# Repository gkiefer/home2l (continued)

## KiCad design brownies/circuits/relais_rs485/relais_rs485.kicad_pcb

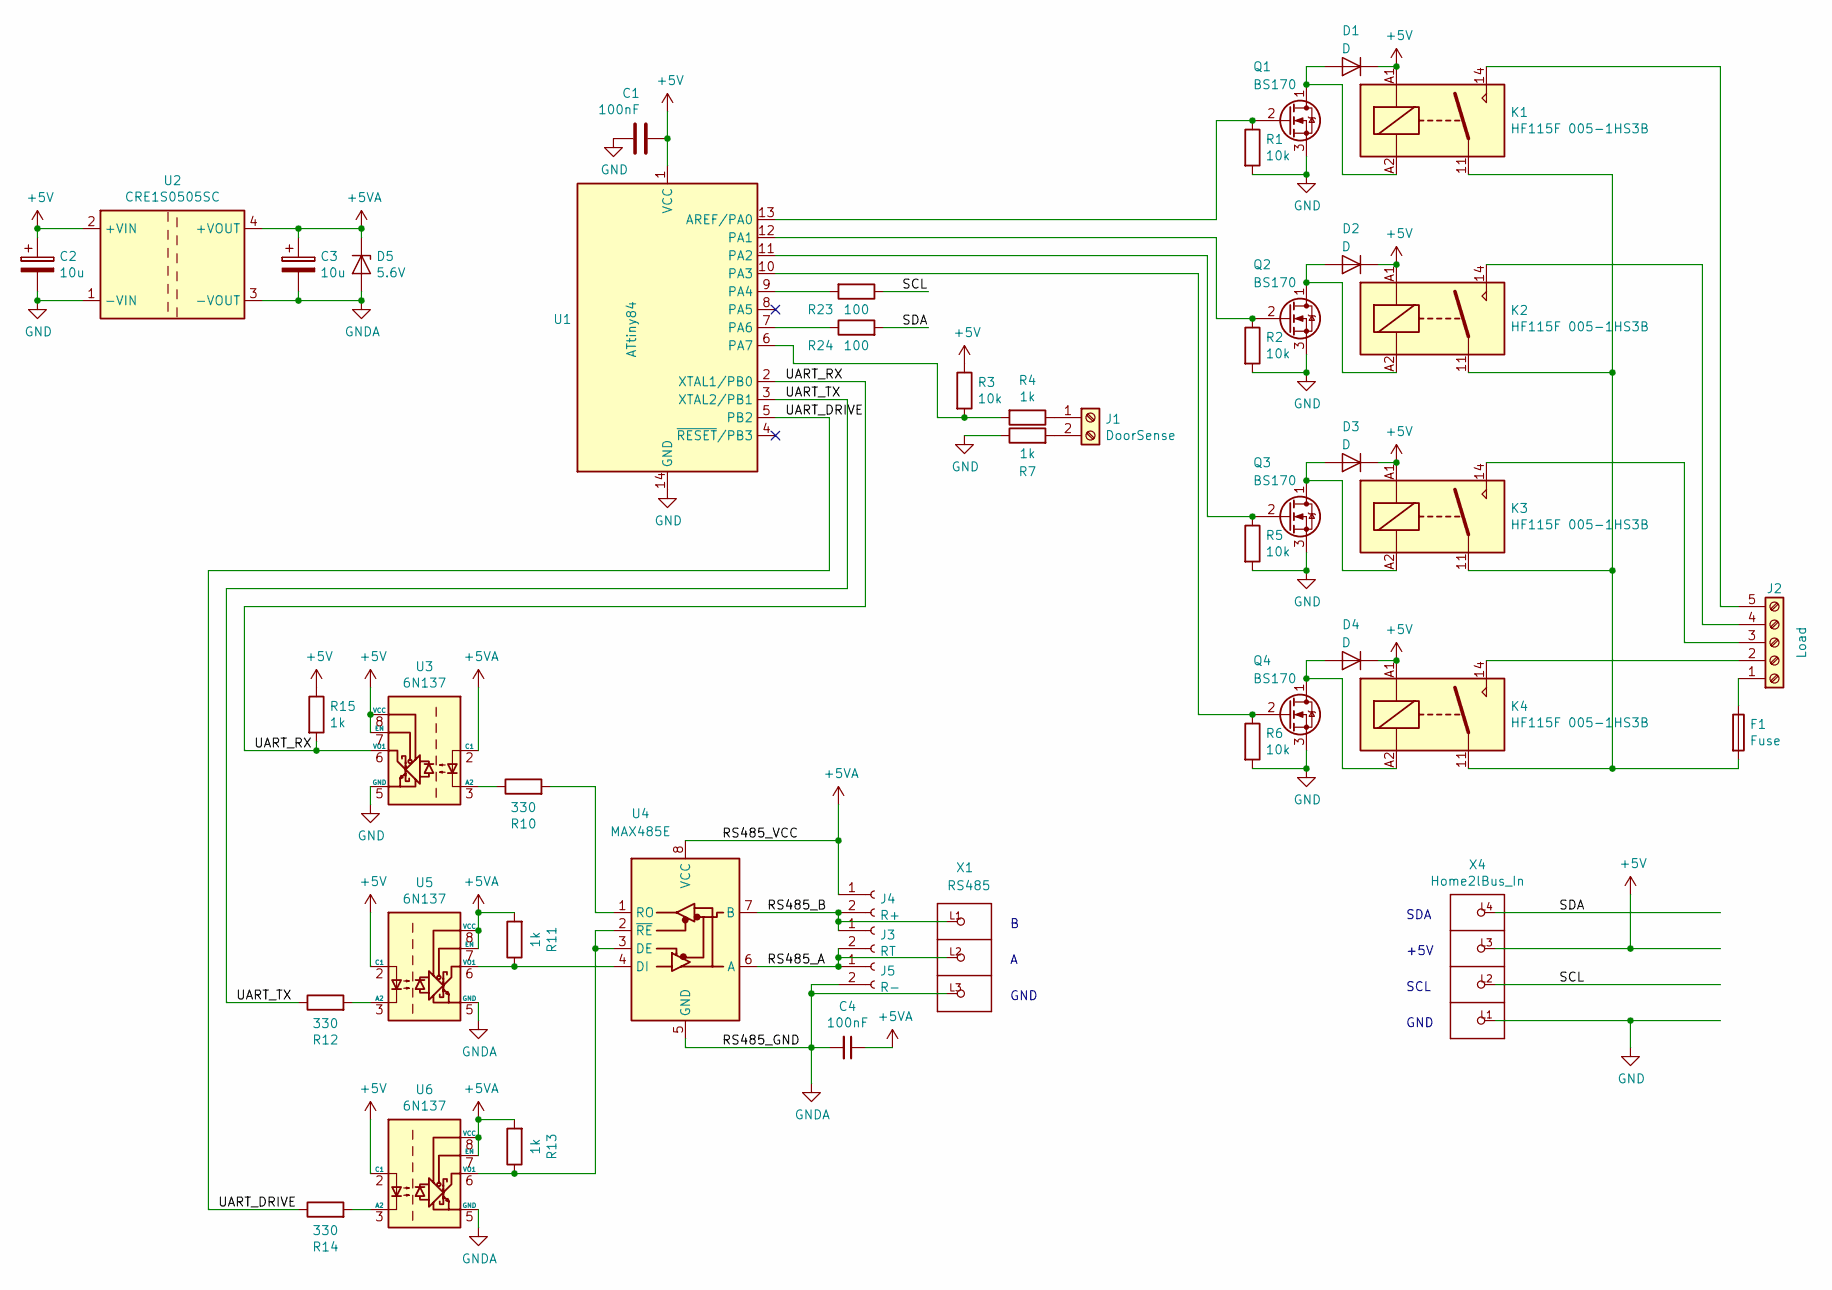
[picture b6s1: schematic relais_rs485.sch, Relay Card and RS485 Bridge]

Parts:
C1: 100nF; C_Disc_D4.3mm_W1.9mm_P5.00mm
C2, C3: 10u; CP_Radial_D5.0mm_P2.50mm
C4: 100nF; C_Axial_L3.8mm_D2.6mm_P7.50mm_Horizontal
D1, D2, D3, D4: D; D_T-1_P5.08mm_Horizontal
D5: 5.6V; D_T-1_P5.08mm_Horizontal
F1: Fuse; Fuseholder_Cylinder-5x20mm_Stelvio-Kontek_PTF78_Horizontal_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
J1: DoorSense; TerminalBlock_Phoenix_MKDS-1,5-2-5.08_1x02_P5.08mm_Horizont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
J2: Load; TerminalBlock_Phoenix_MKDS-1,5-5-5.08_1x05_P5.08mm_Horizont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
J3: RT; PinSocket_1x02_P2.54mm_Vertical
J4: R+; PinSocket_1x02_P2.54mm_Vertical
J5: R-; PinSocket_1x02_P2.54mm_Vertical
K1, K2, K3, K4: HF115F 005-1HS3B; Relay_SPST_Schrack-RP-II-1-16A-FormA_RM5mm
Q1, Q2, Q3, Q4: BS170; TO-92_Inline_Wide
R1, R2, R3, R5, R6: 10k; R_Axial_DIN0204_L3.6mm_D1.6mm_P7.62mm_Horizontal
R4, R7, R11, R13, R15: 1k; R_Axial_DIN0204_L3.6mm_D1.6mm_P7.62mm_Horizontal
R10, R12, R14: 330; R_Axial_DIN0204_L3.6mm_D1.6mm_P7.62mm_Horizontal
R23, R24: 100; R_Axial_DIN0204_L3.6mm_D1.6mm_P7.62mm_Horizontal
U1: ATtiny84; DIP-14_W7.62mm
U2: CRE1S0505SC; Converter_DCDC_muRata_CRE1xxxxxxSC_THT
U3, U5, U6: 6N137; DIP-8_W7.62mm
U4: MAX485E; DIP-8_W7.62mm
X1: RS485; P-250-403
X4: Home2lBus_In; P-250-404

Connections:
+5V: C1.1, C2.1, D1.1 (K), D2.1 (K), D3.1 (K), D4.1 (K), K1.A1, K2.A1, K3.A1, K4.A1, R3.1, R15.1, U1.1 (VCC), U2.2 (+VIN), U3.7 (EN), U3.8 (VCC), U5.2 (C1), U6.2 (C1), X4.L3 (P3)
+5VA: C3.1, C4.1, D5.1 (K), J4.1, R11.2, R13.2, U2.4 (+VOUT), U3.2 (C1), U4.8 (VCC), U5.7 (EN), U5.8 (VCC), U6.7 (EN), U6.8 (VCC)
/RS485_A: J3.2, J5.1, U4.6 (A), X1.L2
/RS485_B: J3.1, J4.2, U4.7 (B), X1.L1
/SCL: R23.1, X4.L2 (P2)
/SDA: R24.2, X4.L4 (P4)
/UART_DRIVE: R14.1, U1.5 (PB2)
/UART_RX: R15.2, U1.2 (XTAL1/PB0), U3.6 (VO1)
/UART_TX: R12.1, U1.3 (XTAL2/PB1)
GND: C1.2, C2.2, Q1.3 (S), Q2.3 (S), Q3.3 (S), Q4.3 (S), R1.2, R2.2, R5.2, R6.2, R7.1, U1.14 (GND), U2.1 (-VIN), U3.5 (GND), X4.L1 (P1)
GNDA: C3.2, C4.2, D5.2 (A), J5.2, U2.3 (-VOUT), U4.5 (GND), U5.5 (GND), U6.5 (GND), X1.L3
unnamed: D1.2 (A), K1.A2, Q1.1 (D)
unnamed: D2.2 (A), K2.A2, Q2.1 (D)
unnamed: D3.2 (A), K3.A2, Q3.1 (D)
unnamed: D4.2 (A), K4.A2, Q4.1 (D)
unnamed: F1.1, J2.1
unnamed: F1.2, K1.11, K2.11, K3.11, K4.11
unnamed: J1.1, R4.1
unnamed: J1.2, R7.2
unnamed: J2.2, K4.14
unnamed: J2.3, K3.14
unnamed: J2.4, K2.14
unnamed: J2.5, K1.14
unnamed: Q1.2 (G), R1.1, U1.13 (AREF/PA0)
unnamed: Q2.2 (G), R2.1, U1.12 (PA1)
unnamed: Q3.2 (G), R5.1, U1.11 (PA2)
unnamed: Q4.2 (G), R6.1, U1.10 (PA3)
unnamed: R3.2, R4.2, U1.6 (PA7)
unnamed: R10.1, U3.3 (A2)
unnamed: R10.2, U4.1 (RO)
unnamed: R11.1, U4.4 (DI), U5.6 (VO1)
unnamed: R12.2, U5.3 (A2)
unnamed: R13.1, U4.2 (~RE), U4.3 (DE), U6.6 (VO1)
unnamed: R14.2, U6.3 (A2)
unnamed: R23.2, U1.9 (PA4)
unnamed: R24.1, U1.7 (PA6)

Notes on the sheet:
SDA
+5V
SCL
GND

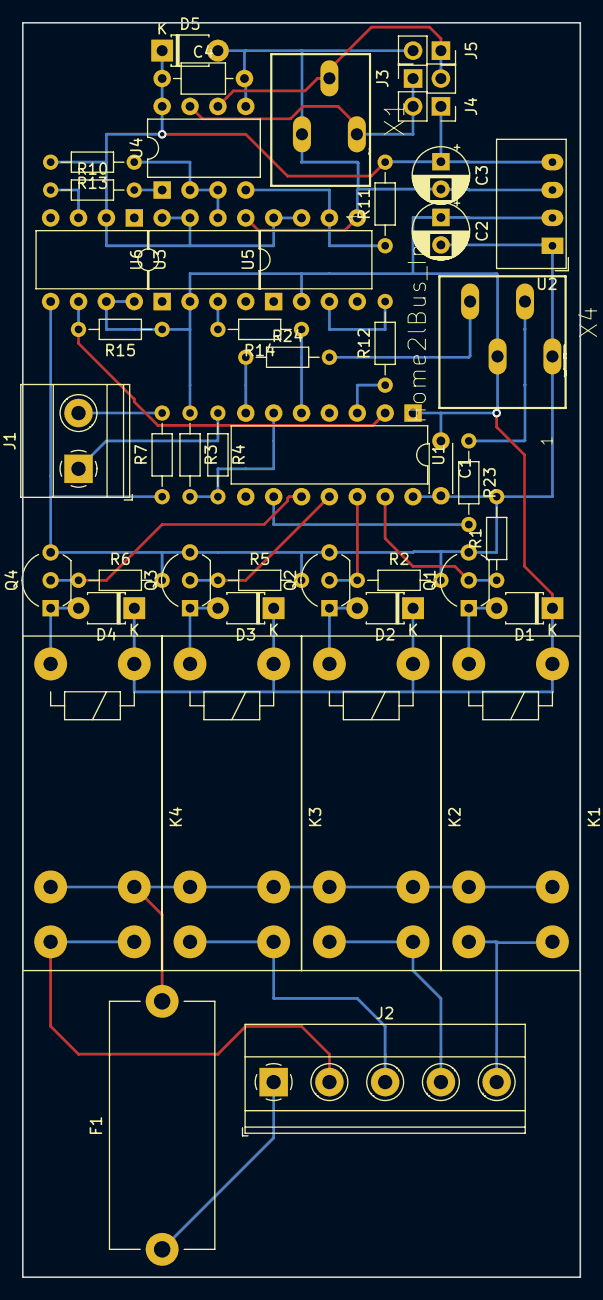
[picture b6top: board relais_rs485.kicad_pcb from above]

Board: 4 copper layers, 50.8 x 114.3 mm, 46 parts (0 on the bottom side), 36 nets.

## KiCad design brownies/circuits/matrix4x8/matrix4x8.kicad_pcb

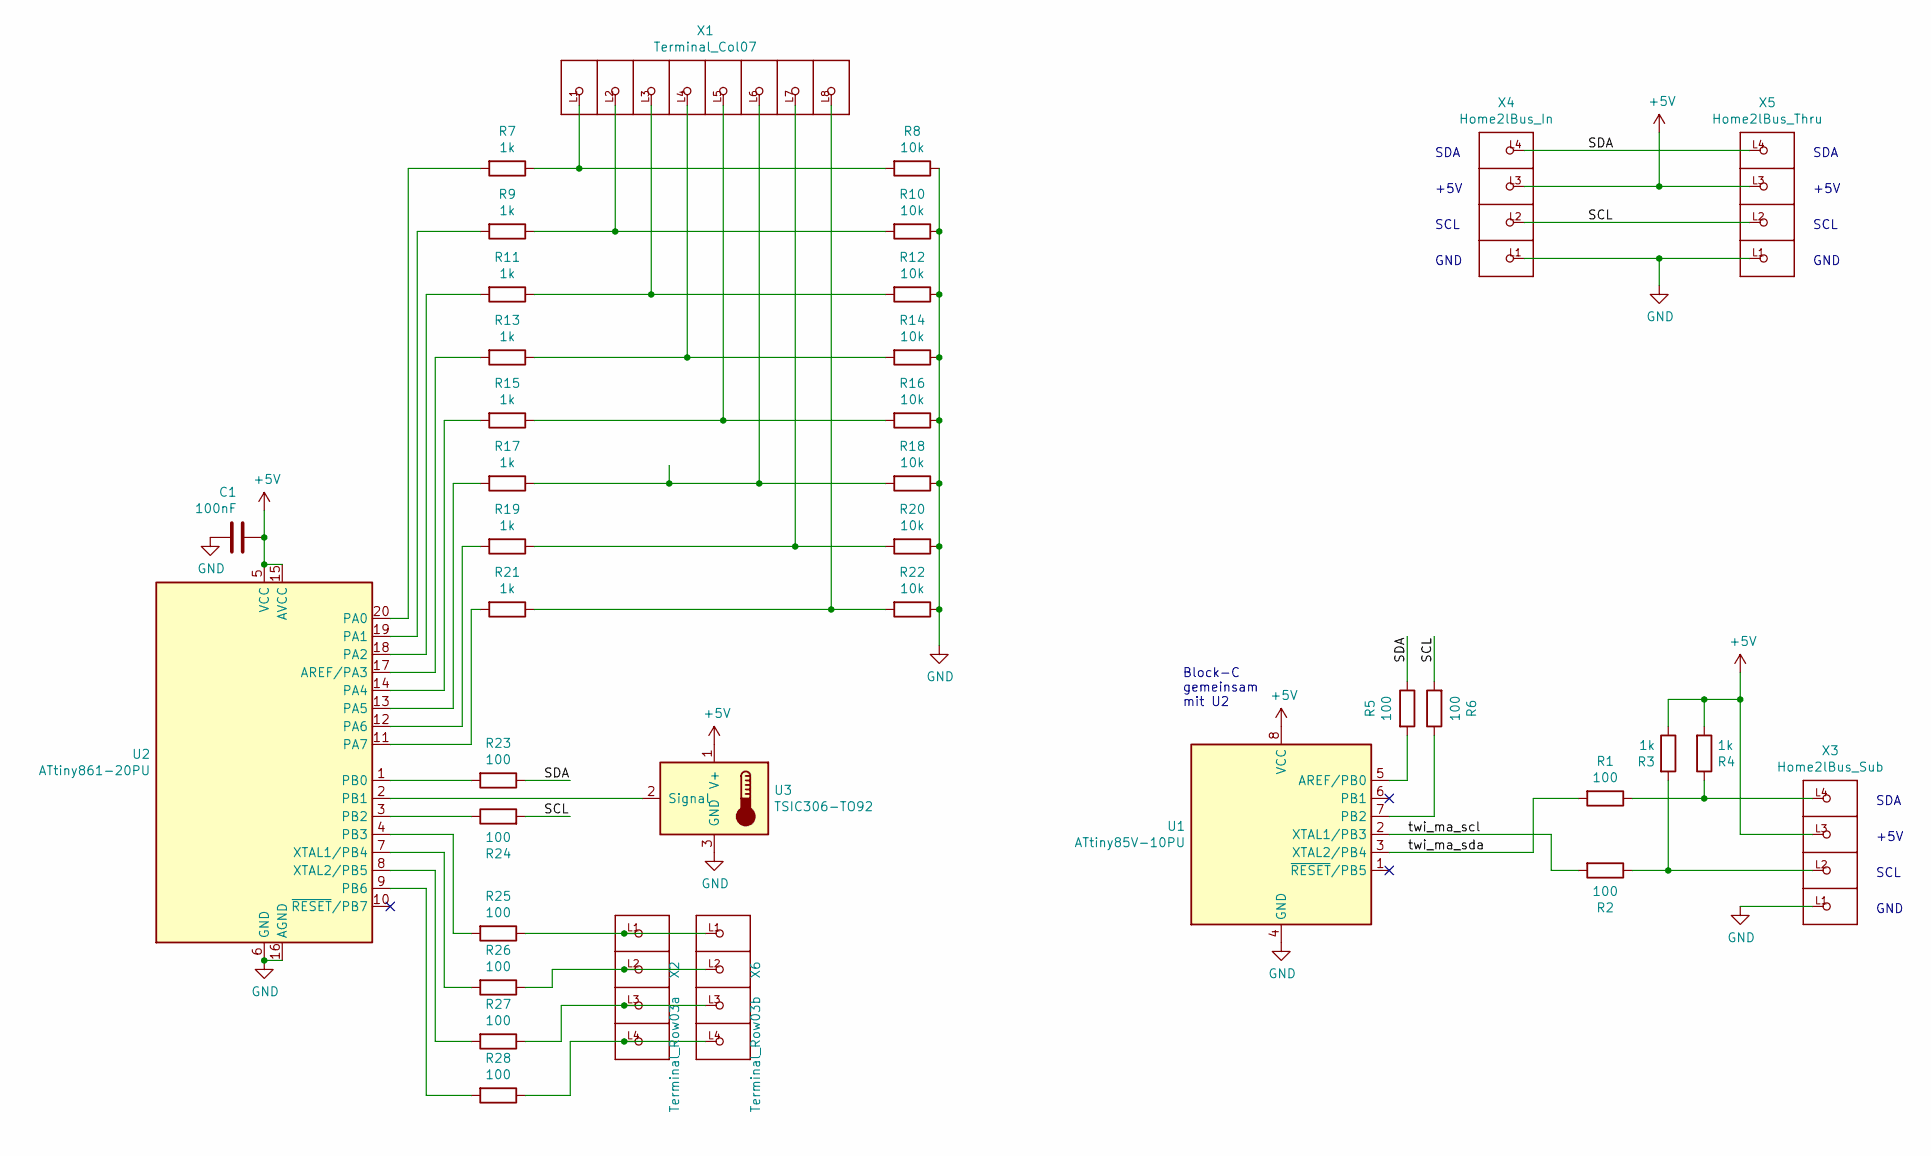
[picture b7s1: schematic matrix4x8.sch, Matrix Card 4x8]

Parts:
C1: 100nF; C_Disc_D4.3mm_W1.9mm_P5.00mm
R1, R2, R5, R6, R23, R24, R25, R26, R27, R28: 100; R_Axial_DIN0207_L6.3mm_D2.5mm_P7.62mm_Horizontal
R3, R4, R7, R9, R11, R13, R15, R17, R19, R21: 1k; R_Axial_DIN0207_L6.3mm_D2.5mm_P7.62mm_Horizontal
R8, R10, R12, R14, R16, R18, R20, R22: 10k; R_Axial_DIN0207_L6.3mm_D2.5mm_P7.62mm_Horizontal
U1: ATtiny85V-10PU; DIP-8_W7.62mm_Socket
U2: ATtiny861-20PU; DIP-20_W7.62mm_Socket
U3: TSIC306-TO92; TO-92_Inline_Wide
X1: Terminal_Col07; P-250-408
X2: Terminal_Row03a; P-250-404
X3: Home2lBus_Sub; P-250-404
X4: Home2lBus_In; P-250-404
X5: Home2lBus_Thru; P-250-404
X6: Terminal_Row03b; P-250-404

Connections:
+5V: C1.1, R3.1, R4.2, U1.8 (VCC), U2.5 (VCC), U2.15 (AVCC), U3.1 (V+), X3.L3 (P3), X4.L3 (P3), X5.L3 (P3)
/SCL: R6.2, R24.2, X4.L2 (P2), X5.L2 (P2)
/SDA: R5.1, R23.1, X4.L4 (P4), X5.L4 (P4)
/twi_ma_scl: R2.2, U1.2 (XTAL1/PB3)
/twi_ma_sda: R1.2, U1.3 (XTAL2/PB4)
GND: C1.2, R8.1, R10.1, R12.1, R14.1, R16.1, R18.1, R20.1, R22.1, U1.4 (GND), U2.6 (GND), U2.16 (AGND), U3.3 (GND), X3.L1 (P1), X4.L1 (P1), X5.L1 (P1)
unnamed: R1.1, R4.1, X3.L4 (P4)
unnamed: R2.1, R3.2, X3.L2 (P2)
unnamed: R5.2, U1.5 (AREF/PB0)
unnamed: R6.1, U1.7 (PB2)
unnamed: R7.1, R8.2, X1.L1 (P1)
unnamed: R7.2, U2.20 (PA0)
unnamed: R9.2, U2.19 (PA1)
unnamed: R9.1, R10.2, X1.L2 (P2)
unnamed: R11.1, R12.2, X1.L3 (P3)
unnamed: R11.2, U2.18 (PA2)
unnamed: R13.1, R14.2, X1.L4 (P4)
unnamed: R13.2, U2.17 (AREF/PA3)
unnamed: R15.1, R16.2, X1.L5 (P5)
unnamed: R15.2, U2.14 (PA4)
unnamed: R17.1, R18.2, X1.L6 (P6)
unnamed: R17.2, U2.13 (PA5)
unnamed: R19.1, R20.2, X1.L7 (P7)
unnamed: R19.2, U2.12 (PA6)
unnamed: R21.1, R22.2, X1.L8 (P8)
unnamed: R21.2, U2.11 (PA7)
unnamed: R23.2, U2.1 (PB0)
unnamed: R24.1, U2.3 (PB2)
unnamed: R25.1, X2.L1 (P1), X6.L1 (P1)
unnamed: R25.2, U2.4 (PB3)
unnamed: R26.1, X2.L2 (P2), X6.L2 (P2)
unnamed: R26.2, U2.7 (XTAL1/PB4)
unnamed: R27.1, X2.L3 (P3), X6.L3 (P3)
unnamed: R27.2, U2.8 (XTAL2/PB5)
unnamed: R28.1, X2.L4 (P4), X6.L4 (P4)
unnamed: R28.2, U2.9 (PB6)
unnamed: U2.2 (PB1), U3.2 (Signal)

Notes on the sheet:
SDA
+5V
SCL
GND
Block-C gemeinsam mit U2

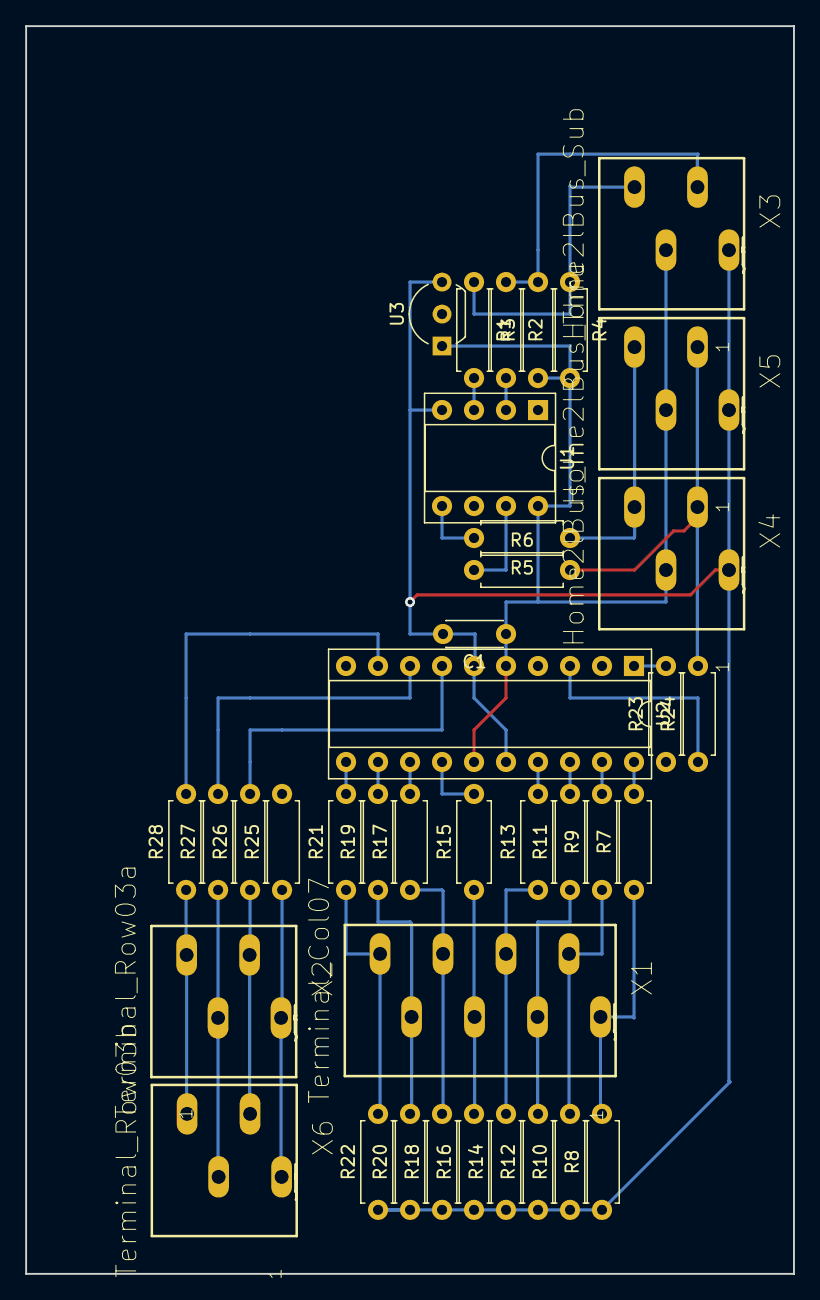
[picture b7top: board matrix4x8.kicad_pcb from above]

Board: 4 copper layers, 61.0 x 99.1 mm, 38 parts (0 on the bottom side), 37 nets.

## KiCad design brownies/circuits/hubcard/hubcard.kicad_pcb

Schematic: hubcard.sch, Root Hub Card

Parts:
C1: 100nF; C_Disc_D4.3mm_W1.9mm_P5.00mm
D1, D2, D3: 6,8V; D_DO-34_SOD68_P7.62mm_Horizontal
J1: Conn_02x10_Odd_Even; PinHeader_2x10_P2.54mm_Horizontal_Pins_Reversed
J2: Conn_02x04_Odd_Even; PinHeader_2x04_P2.54mm_Horizontal
J3: Conn_01x03_Male; PinHeader_1x03_P2.54mm_Vertical
J4: Conn_01x04_Male; PinHeader_1x04_Home2lBus
Q1: IRF5305; TO-220-3_Vertical
R1: 47k; R_Axial_DIN0207_L6.3mm_D2.5mm_P7.62mm_Horizontal
R2, R3: 100; R_Axial_DIN0207_L6.3mm_D2.5mm_P7.62mm_Horizontal
R4, R5: 1k; R_Axial_DIN0207_L6.3mm_D2.5mm_P7.62mm_Horizontal
U1: ATtiny85V-10PU; DIP-8_W7.62mm_Socket

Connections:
+5V: C1.1, J3.2, Q1.3 (S), R1.1, U1.8 (VCC)
+12V: J1.1, J1.2, J1.3, J1.4
/SCL: J1.17, J1.18, U1.7 (PB2)
/SDA: J1.19, J1.20, U1.5 (AREF/PB0)
/gpio0: Q1.1 (G), R1.2, U1.6 (PB1)
/twi_ma_scl: R2.2, U1.2 (XTAL1/PB3)
/twi_ma_sda: R3.2, U1.3 (XTAL2/PB4)
GND: C1.2, D1.2, D2.2, D3.2, J1.5, J1.6, J1.7, J1.8, J4.1, U1.4 (GND)
unnamed: D1.1, J4.3, Q1.2 (D), R4.1, R5.1
unnamed: D2.1, J4.4, R3.1, R5.2
unnamed: D3.1, J4.2, R2.1, R4.2
unnamed: J1.9, J1.10, J1.11, J1.12, J3.3
unnamed: J1.13, J1.14, J3.1
unnamed: J1.15, J1.16

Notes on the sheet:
SDA
+5V
SCL
GND

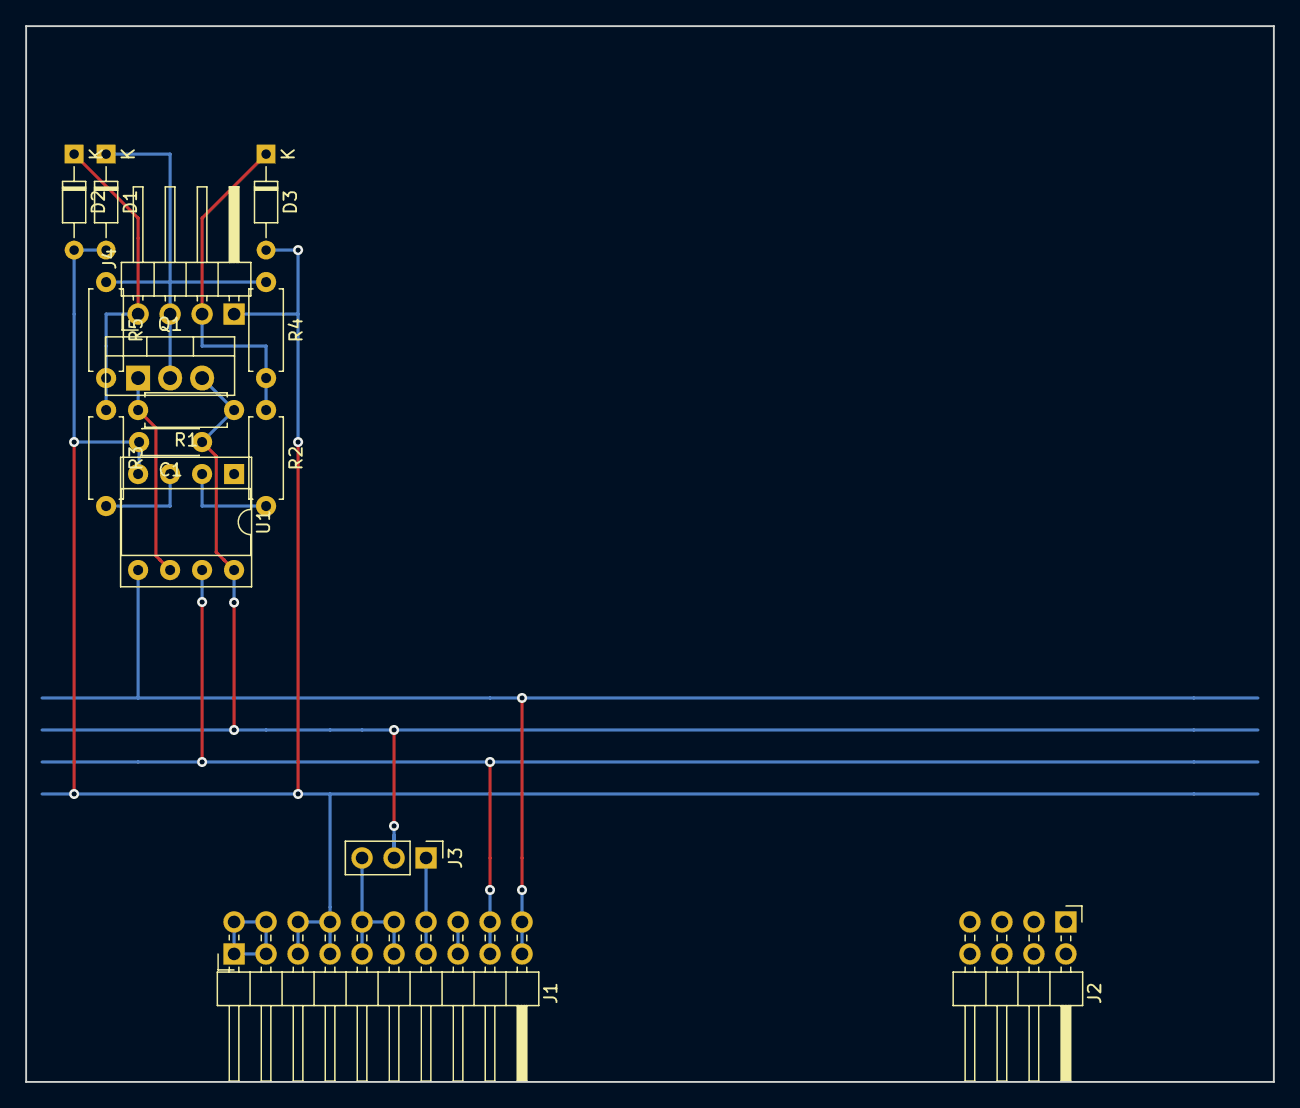
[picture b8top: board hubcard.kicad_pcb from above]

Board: 2 copper layers, 99.1 x 83.8 mm, 15 parts (0 on the bottom side), 14 nets.

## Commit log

2018-11-27 Set theme jekyll-theme-minimal
2018-11-27 Add all source files
2018-11-28 Add preliminary book and showcase; Some cleanup
2018-11-29 doc: Test and complete the tutorial
2018-11-30 Finalize README.md; Add binary docs; Release v0.9
2018-11-30 Add .gitattributes
2018-12-03 Add search engine authentication files; Tweak documentation
2020-02-07 Add major new features: Brownies, floor plan, Docker image, improved tutorial, improved Android app; Many improvements and bug fixes
2020-02-07 Add binary docs for v1.0
2020-02-23 Add new generic resource dialog (wallclock/floorplan UI); Various improvements and minor fixes
    - resources: Add 'CResource::GetRequest()' to query an active request by its GID
    - resources: Make access methods with relaxed typing more flexible, improve CRcRequest::ToStr() and CRcRequest::Convert()
    - wallclock/floorplan: Add new generic resource dialog
    - wallclock/floorplan: Implement default options for enabling rwin actuators and shades
    - wallclock/ui: Improve base API, CButton, CListbox, CMessageBox
    - wallclock/ui: Add 'CInputScreen'
2020-03-03 wallclock: Fix crash (regression) on floorplan startup; Update tutorial instructions on the floorplan UI
2020-03-24 Dockerfile: Allow building without special args (BUILD_VERSION); Tweak documentation
2020-05-08 Allow standalone-usage of tools; Improve Brownie firmware; Fix wallclock/calendar error reporting
    - Makefile: Add Brownies to the "basic" target
    - Make configuration files 'home2l.conf', 'resources.conf', 'brownies.conf' optional by setting their names to an empty string.
    - brownies/driver: Add support for inverted window sensor inputs
    - brownies/avr: Add support for efficient "matrix" with one row (no stimulation)
    - brownies: Add circuits: matrix1x7, matrix2x6
    - brownies: Add 'wins' firmware for a (roof) window with shades and actuator
2020-08-14 Add MQTT gatway driver; Add rain warning to weather driver; Improve floor plan UI; Many minor improvements
2020-08-15 Add MQTT gateway driver; Add rain warning to weather driver; Improve floor plan UI; Many minor improvements
2020-08-18 Fix some regressions (UI/listbox; UI/floorplan return after alert; resources: false reporting of unkowns)
2020-09-05 Add EnEocean driver; Several minor improvements
    Compatibilty notes:
    - Renamed environment settings:
    "floorplan.requestAttrs" -> "floorplan.reqAttrs"
    "br.shades.requestAttrs" -> "br.shades.reqAttrs"
    - Renamed floorplan resource names:
    roof window (rwin): "actuator" -> "opener"
2021-01-10 Add UART feature for Brownies; Improve Python API, Home2L Shell, and WallClock UI
    - Python API: Add connectors and gates, many minor improvements to simplify rules writing
    - Shell: Add call aliases and 'get'/'wait' commands for scripted use
    - Brownies: Add UART module to communicate with remote RS485 devices
    - WallClock: Unified color scheme, several UI improvements
    - many minor improvements
    Compatibility note:
2021-06-30 New ADC module for Brownies; New PJSIP phone backend for DoorMan and WallClock; More Python API improvments
    - wallclock/doorman: Add PJSIP phone backend, make PJSIP the default
    - wallclock: Update to compile with Android NDK 21e; Upgrade SDL2 to 2.0.8
    - wallclock: New floor plan gadgets (gtDoor, gtGate, gtWarning)
    - wallclock: Add "interactive" option for gadgets of type window/door/gate and icon-like gadgets
    - wallclock: Many UI improvements
    - resources: Make resource persistence and default requests configurable in 'resources.conf'
2021-12-10 Support for Debian 11 (Bullseye), Resources library improvements, many minor improvements
    Makefile: Add profiling build option, replace RELEASE with DEBUG
    common: Add 'CList*' container classes, cleanup and improve container classes
    common: Cleanup 'TTicks' API, eliminate extra type 'TTicksMonotonic'
    common: Eliminate TTS variants of functions, cleanup code
    common: Fix and improve string escaping, especially for stored environment and persistent resources
    common/daemon: Cleanup process termination in 'CShellBare' and 'home2l-daemon'
2022-07-22 Design and layout for a card with 11 roothubs
    Each of the 11 hubs may be separated and used standalone
    Project structured as KiCad 6 flat hierarchy
2022-07-29 brownies/contrib: Rename to snake case
2022-07-29 brownies/circuits/contrib/roothubs: Add README
2022-07-30 Added e-mail-address to README
2022-07-30 Added html bom and interactive place (Bestückungs) tool
2022-07-31 Design and layout for a card with 11 roothubs (#1)
    Add brownies/circuits/contrib/roothubs: Design and layout for a card with 11 roothubs (contributed by Axel Rau)
2022-08-31 Various minor fixes and improvements; Ready for version 1.2
2023-03-19 fix incorrect payload size for 'mosquitto_publish'
2023-03-19 Use 'SetF" for MQTT will & birth payload
2023-03-19 Allow more than one exported resource
2023-03-21 mqtt: Fix missing subscriptions on MQTT exports
2023-04-15 Various improvements and bug fixes
    - Makefile: Re-arrange configuration presets, make presets compile only for the native architecture
    - tools: Add tool 'home2l-usbtree' to supervise USB devices
    - mqtt: Add option 'mqtt.nullTerminatePayload' and send payloads without terminating null characters by default (see https://github.com/gkiefer/home2l/pull/3#issuecomment-1480084724)
    - weather: Adapt radar eye for changed directory structure on opendata.dwd.de
    - resources: Add optional 'data' argument to 'RunOnUpdate()'
    - brownies: Fix "feature" option in database; Add "soft" option for Brownie booting
2023-04-17 mqtt: Fix regression related to payload length
2023-04-22 Added Retry code for failing ELV-USB-I2C device in IfElvI2cInit
2023-09-25 Added FAQ
2023-12-09 Correction of mqttWillPayload length
2023-12-09 Correction of mqttWillPayload length (#6)
2024-05-25 Various improvements and some fixes
    - Various adaptations for Debian 12 (Bookworm)
    - showcase: Move all demo-related parts to a new subproject 'showcase'
    - resources: Extend API, make state attribute methods like 'isBusy()' available in 'CResource'
    - resources: Add new type 'rcPower'; add 'CRcValueState::ToHuman()'
    - resources: Add support for info/warning messages by script drivers; Fix driving for keep-running drivers; Add capturing of stderr
    - brownies: Add retry loop to 'IfElvI2cInit()', closes Github pull request #4 ("Retry code for failing ELV-USB-I2C device")
2024-05-27 Renamed and updated for KiCad 8: roothubs
2024-05-27 Added 4 circuits to contrib
2024-05-31 Corrected typo in brownies/circuits/contrib/shades_and_relais/README
2024-05-31 Another typo in README
2024-06-01 1 modified and 4 new circuits in brownies/circuits/contrib (w. fixed typos) (#8)
    * Renamed and updated for KiCad 8: roothubs
    * Added 4 circuits to contrib
    * Corrected typo in brownies/circuits/contrib/shades_and_relais/README
    * Another typo in README
2025-08-22 Adapt for Debian 13 (Trixie); Add iCal support to calendar (beta)
    - Make necessary changes for Debian 13, drop i386 support
    - wallclock/calendar: Add iCal support
    BREAKING CHANGES IN CONFIG ('home2l.conf'):
    calendar.dir -> calendar.remindDir
    calendar.name -> calendar.id
    - wallclock/music,drivers/mpd: Clean up configuration variables;
2025-08-22 wallclock: Fix 'generate-icons.sh' (regression)
